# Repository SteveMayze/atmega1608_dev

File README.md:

# ATMega1608 Dev KiCad Automation

This project includes release automation for fabrication deliverables.

The automation entrypoints are intentionally stored at repository root so GitHub Actions can discover workflows correctly.

## Current automation goal

When a Git tag matching `r#.#.#` is pushed (example: `r0.1.0`), GitHub Actions will:

1. Set the KiCad text variable `RELEASE` in the project file.
2. Generate Gerber and drill files using `kicad-cli`.
3. Write deliverables to `gerber/`.
4. Upload artifacts and attach a ZIP to the GitHub release.

## Files added for automation

- `.github/workflows/release-gerbers.yml`: Release workflow triggered by version tags.
- `scripts/generate_release_artifacts.py`: Single entrypoint script for local and CI generation.
- `release-artifacts.json`: User-editable release configuration, including Gerber include layers.
- `PROJECT_TRACKING.md`: Task and roadmap tracking.

## Local usage

### Prerequisites

- KiCad installed with `kicad-cli` available on PATH.
- Python 3.9+.

If `kicad-cli` is not on PATH, set:

- macOS/Linux: `export KICAD_CLI=/full/path/to/kicad-cli`
- Windows (PowerShell): `$env:KICAD_CLI="C:\\Path\\To\\kicad-cli.exe"`

### Configure Gerber include layers

Edit `release-artifacts.json` and set:

- `project.path`: Relative path to your KiCad `.kicad_pro` file.
- `gerber.include_layers`: Layers to include in Gerber export.

Example:

```json
{
	"project": {
		"path": "kicad/ATMega1608_Dev/ATMega1608_Dev.kicad_pro"
	},
	"gerber": {
		"include_layers": [
			"F.Cu",
			"B.Cu",
			"F.Mask",
			"B.Mask",
			"F.SilkS",
			"B.SilkS",
			"Edge.Cuts"
		]
	}
}
```

This list is passed to `kicad-cli` as the `--layers` argument.
The script validates configured layer names against the board's `(layers ...)` list in the PCB file and fails early if any configured layer is invalid.

### Generate Gerbers for a release tag

```bash
python3 scripts/generate_release_artifacts.py --tag r0.1.0
```

This will update `RELEASE` to `0.1.0` and generate output in `gerber/`.

If needed, `--project` can still be passed to override `project.path` from config.

### Generate without updating `RELEASE`

```bash
python3 scripts/generate_release_artifacts.py --tag r0.1.0 --no-update-release-variable
```

### Dry run (no generation, just prints commands)

```bash
python3 scripts/generate_release_artifacts.py --tag r0.1.0 --dry-run
```

## Release trigger

Push a release tag:

```bash
git tag r0.1.0
git push origin r0.1.0
```

The workflow runs automatically for tags matching `r*.*.*`.

## CI KiCad version

This project currently targets a KiCad 10 board file format, so CI installs KiCad nightly in
GitHub Actions before generating artifacts.

The workflow uses `release-artifacts.json` for project discovery and does not hardcode the
`.kicad_pro` location.

## Future extension

The script already includes optional flags for future needs:

- `--schematic-pdf` to export schematic PDF.
- `--board-pdf` to export PCB layout PDF.

These are optional now and can be enabled later in the workflow.

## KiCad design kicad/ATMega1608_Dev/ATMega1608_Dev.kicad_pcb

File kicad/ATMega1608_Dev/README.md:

# ATMega1608 Dev KiCad Automation

This project includes release automation for fabrication deliverables.

## Current automation goal

When a Git tag matching `r#.#.#` is pushed (example: `r0.1.0`), GitHub Actions will:

1. Set the KiCad text variable `RELEASE` in the project file.
2. Generate Gerber and drill files using `kicad-cli`.
3. Write deliverables to `gerber/`.
4. Upload artifacts and attach a ZIP to the GitHub release.

## Files added for automation

- `.github/workflows/release-gerbers.yml`: Release workflow triggered by version tags.
- `scripts/generate_release_artifacts.py`: Single entrypoint script for local and CI generation.
- `release-artifacts.json`: User-editable release configuration, including Gerber include layers.
- `PROJECT_TRACKING.md`: Task and roadmap tracking.

## Local usage

### Prerequisites

- KiCad installed with `kicad-cli` available on PATH.
- Python 3.9+.

If `kicad-cli` is not on PATH, set:

- macOS/Linux: `export KICAD_CLI=/full/path/to/kicad-cli`
- Windows (PowerShell): `$env:KICAD_CLI="C:\\Path\\To\\kicad-cli.exe"`

### Configure Gerber include layers

Edit `release-artifacts.json` and set `gerber.include_layers` to match your manufacturing output needs.

Example:

```json
{
	"gerber": {
		"include_layers": [
			"F.Cu",
			"B.Cu",
			"F.Mask",
			"B.Mask",
			"F.SilkS",
			"B.SilkS",
			"Edge.Cuts"
		]
	}
}
```

This list is passed to `kicad-cli` as the `--layers` argument.
The script validates configured layer names against the board's `(layers ...)` list in the PCB file and fails early if any configured layer is invalid.

### Generate Gerbers for a release tag

```bash
python3 scripts/generate_release_artifacts.py --tag r0.1.0
```

This will update `RELEASE` to `0.1.0` and generate output in `gerber/`.

### Generate without updating `RELEASE`

```bash
python3 scripts/generate_release_artifacts.py --tag r0.1.0 --no-update-release-variable
```

### Dry run (no generation, just prints commands)

```bash
python3 scripts/generate_release_artifacts.py --tag r0.1.0 --dry-run
```

## Release trigger

Push a release tag:

```bash
git tag r0.1.0
git push origin r0.1.0
```

The workflow runs automatically for tags matching `r*.*.*`.

## Future extension

The script already includes optional flags for future needs:

- `--schematic-pdf` to export schematic PDF.
- `--board-pdf` to export PCB layout PDF.

These are optional now and can be enabled later in the workflow.

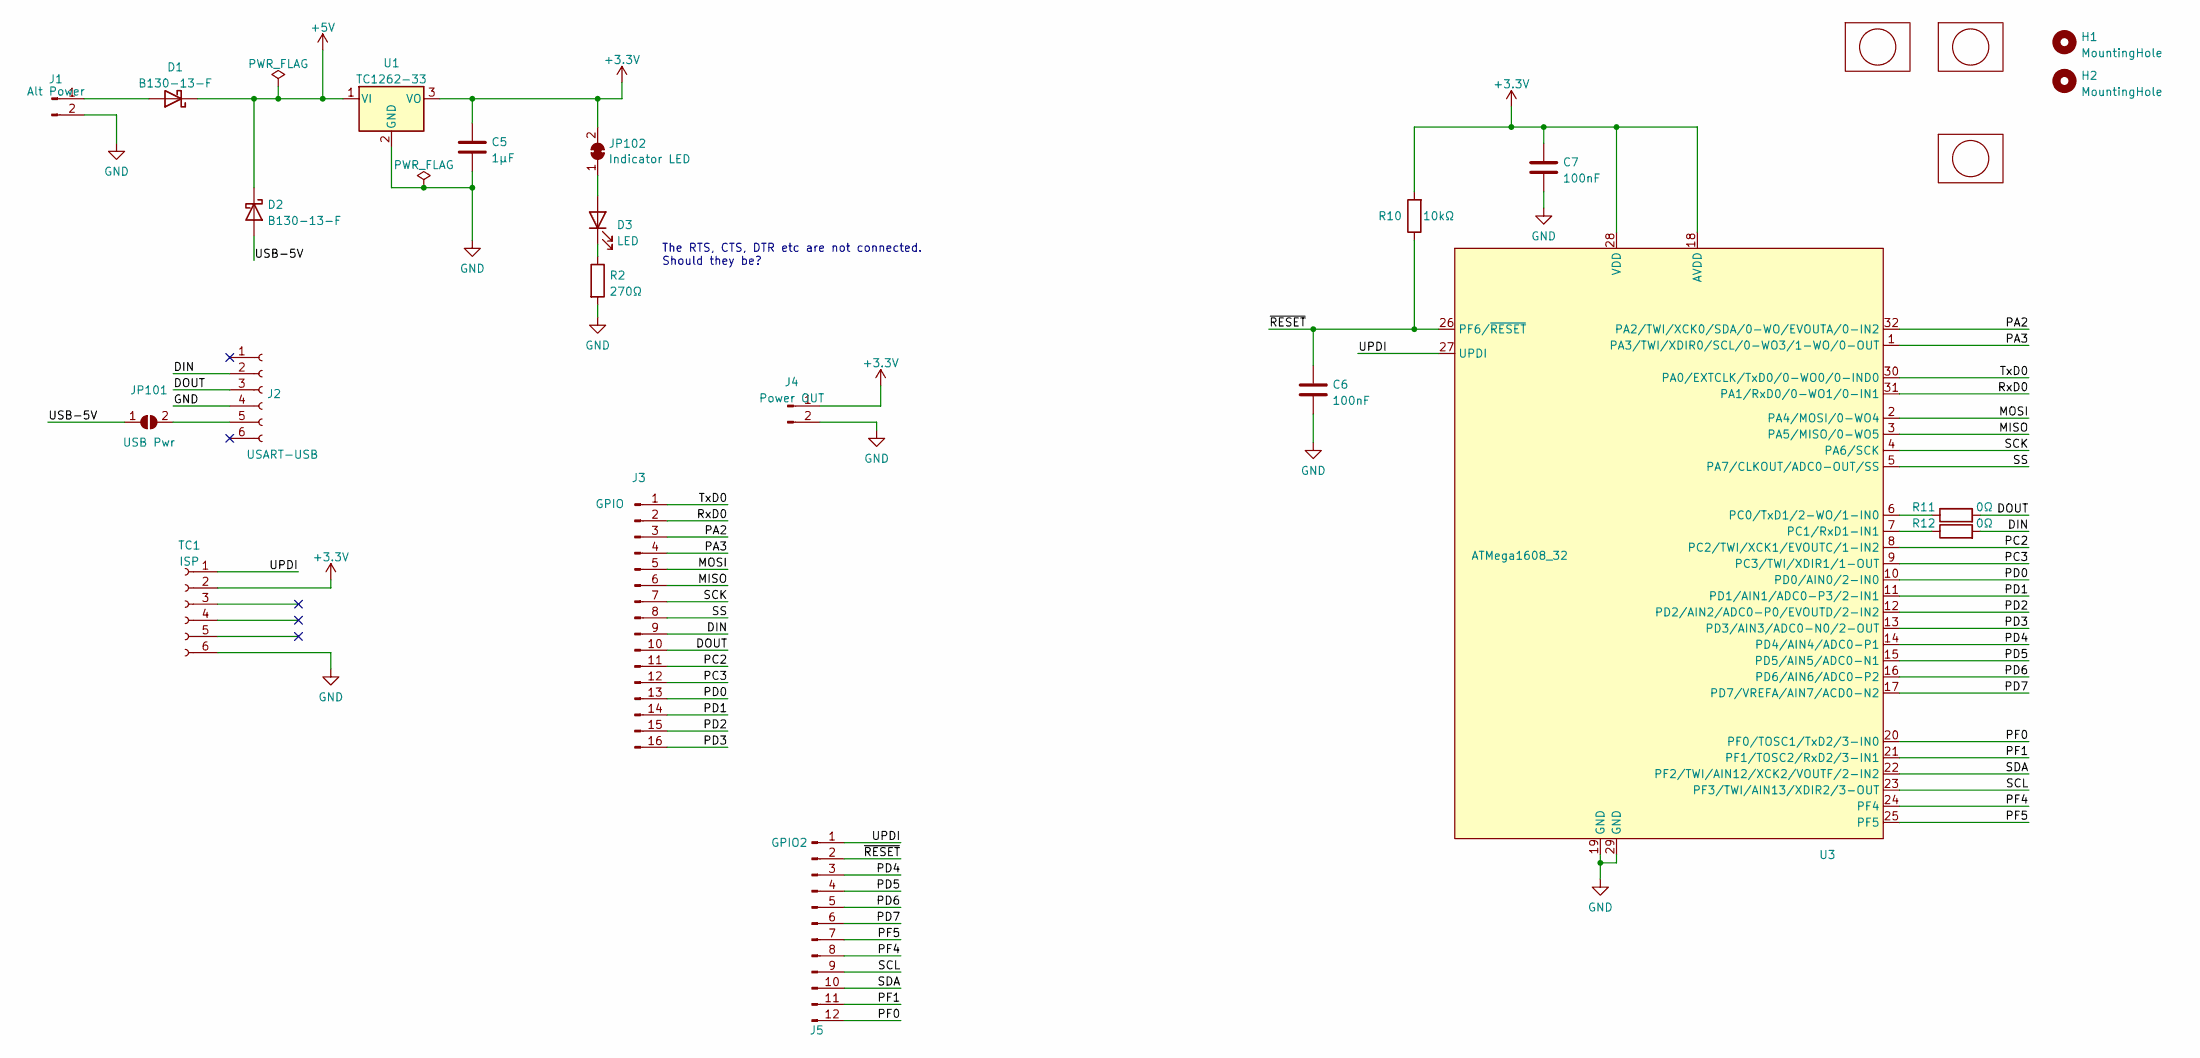
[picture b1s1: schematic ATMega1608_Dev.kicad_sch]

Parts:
C5: 1μF; C_0805_2012Metric_Pad1.18x1.45mm_HandSolder
C6, C7: 100nF; C_0805_2012Metric
D1, D2: B130-13-F; D_SMA; MPN B130-13-F
D3: LED; LED_0805_2012Metric
H1, H2: MountingHole; MountingHole_2.7mm_M2.5
J1: Alt Power; PinHeader_1x02_P2.54mm_Vertical
J2: USART-USB; PinSocket_1x06_P2.54mm_Vertical
J3: GPIO; PinHeader_1x16_P2.54mm_Vertical
J4: Power OUT; PinHeader_1x02_P2.54mm_Vertical
J5: GPIO2; PinHeader_1x12_P2.54mm_Vertical
JP101: USB Pwr; PinHeader_1x02_P2.54mm_Vertical
JP102: Indicator LED; SolderJumper-2_P1.3mm_Bridged_RoundedPad1.0x1.5mm
LG1, LG3: logo; MyBasic_rounded_50_1
LG2: logo; KiCad-Logo_5mm_SilkScreen
R2: 270Ω; R_0805_2012Metric
R10: 10kΩ; R_0805_2012Metric
R11, R12: 0Ω; R_0805_2012Metric
TC1: ISP; Tag-Connect EC06
U1: TC1262-33; SOT-223-3_TabPin2
U3: ATMega1608_32; TQFP-32_7x7mm_P0.8mm

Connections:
+3.3V: C5.1, C7.1, J4.1, JP102.2 (B), R10.2, TC1.2, U1.3 (VO), U3.18 (AVDD), U3.28 (VDD)
+5V: D1.1 (K), D2.1 (K), U1.1 (VI)
/DIN: J2.2, J3.9, R12.2
/DOUT: J2.3, J3.10, R11.2
/MISO: J3.6, U3.3 (PA5/MISO/0-WO5)
/MOSI: J3.5, U3.2 (PA4/MOSI/0-WO4)
/PA2: J3.3, U3.32 (PA2/TWI/XCK0/SDA/0-WO/EVOUTA/0-IN2)
/PA3: J3.4, U3.1 (PA3/TWI/XDIR0/SCL/0-WO3/1-WO/0-OUT)
/PC2: J3.11, U3.8 (PC2/TWI/XCK1/EVOUTC/1-IN2)
/PC3: J3.12, U3.9 (PC3/TWI/XDIR1/1-OUT)
/PD0: J3.13, U3.10 (PD0/AIN0/2-IN0)
/PD1: J3.14, U3.11 (PD1/AIN1/ADC0-P3/2-IN1)
/PD2: J3.15, U3.12 (PD2/AIN2/ADC0-P0/EVOUTD/2-IN2)
/PD3: J3.16, U3.13 (PD3/AIN3/ADC0-N0/2-OUT)
/PD4: J5.3, U3.14 (PD4/AIN4/ADC0-P1)
/PD5: J5.4, U3.15 (PD5/AIN5/ADC0-N1)
/PD6: J5.5, U3.16 (PD6/AIN6/ADC0-P2)
/PD7: J5.6, U3.17 (PD7/VREFA/AIN7/ACD0-N2)
/PF0: J5.12, U3.20 (PF0/TOSC1/TxD2/3-IN0)
/PF1: J5.11, U3.21 (PF1/TOSC2/RxD2/3-IN1)
/PF4: J5.8, U3.24 (PF4)
/PF5: J5.7, U3.25 (PF5)
/RxD0: J3.2, U3.31 (PA1/RxD0/0-WO1/0-IN1)
/SCK: J3.7, U3.4 (PA6/SCK)
/SCL: J5.9, U3.23 (PF3/TWI/AIN13/XDIR2/3-OUT)
/SDA: J5.10, U3.22 (PF2/TWI/AIN12/XCK2/VOUTF/2-IN2)
/SS: J3.8, U3.5 (PA7/CLKOUT/ADC0-OUT/SS)
/TxD0: J3.1, U3.30 (PA0/EXTCLK/TxD0/0-WO0/0-IND0)
/UPDI: J5.1, TC1.1, U3.27 (UPDI)
/USB-5V: D2.2 (A), JP101.1 (A)
/~RESET: C6.1, J5.2, R10.1, U3.26 (PF6/~RESET)
GND: C5.2, C6.2, C7.2, J1.2, J2.4, J4.2, R2.2, TC1.6, U1.2 (GND), U3.19 (GND), U3.29 (GND)
unnamed: D1.2 (A), J1.1
unnamed: D3.2 (A), JP102.1 (A)
unnamed: D3.1 (K), R2.1
unnamed: J2.5, JP101.2 (B)
unnamed: R11.1, U3.6 (PC0/TxD1/2-WO/1-IN0)
unnamed: R12.1, U3.7 (PC1/RxD1-IN1)

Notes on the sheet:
The RTS, CTS, DTR etc are not connected. Should they be?

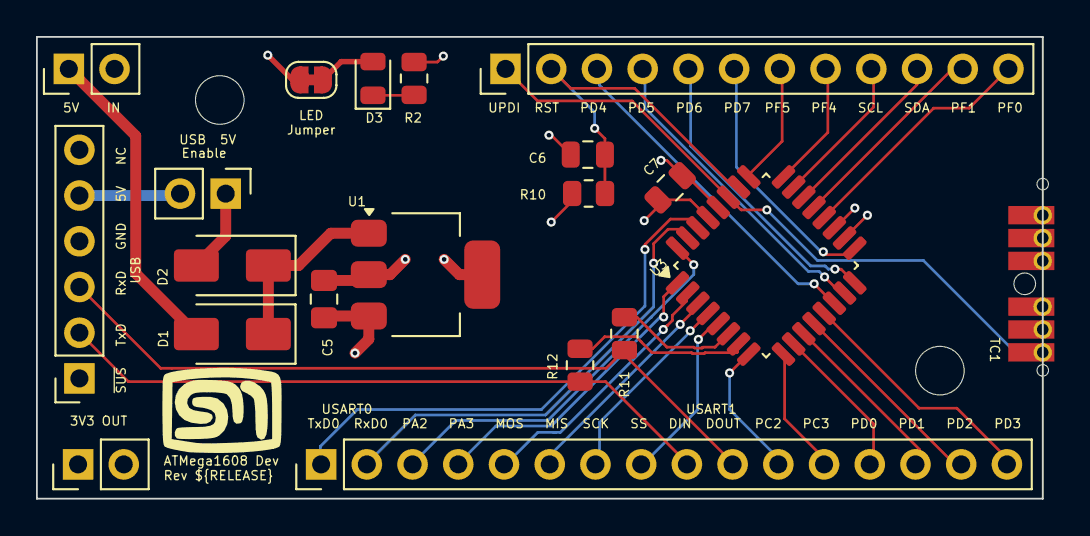
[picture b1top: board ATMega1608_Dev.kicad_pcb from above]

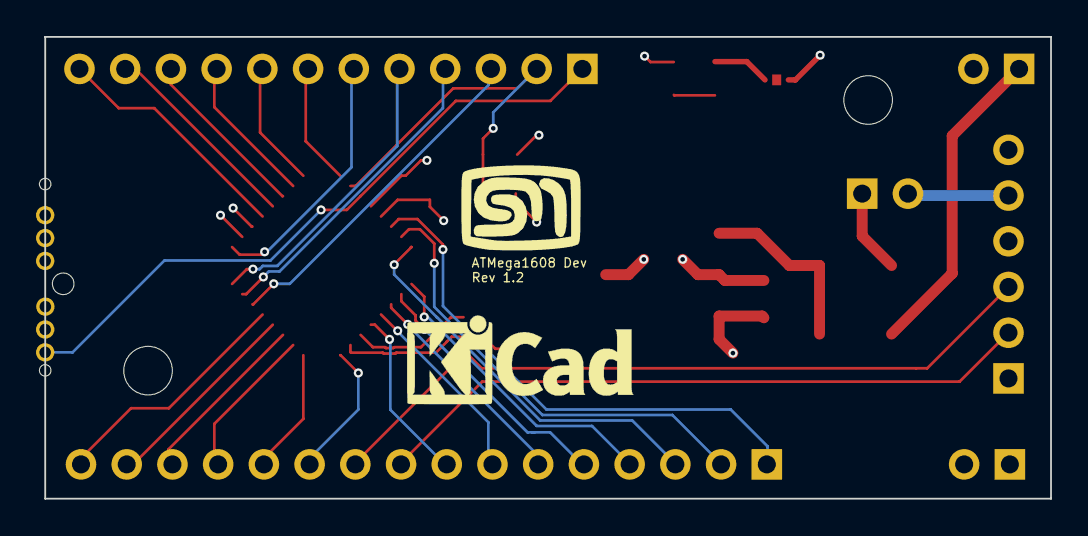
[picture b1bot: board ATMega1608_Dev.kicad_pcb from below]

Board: 4 copper layers, 55.9 x 25.7 mm, 25 parts (2 on the bottom side), 38 nets.

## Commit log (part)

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2023-01-21 Initial checkin
2023-01-21 Schematic complete
2023-01-21 Started on the layout
2023-01-22 The layout is complete - pending verification of USB interface
2023-03-05 Fixes some labeling issues
2023-03-20 Troubleshooting and diagnostic updates
2023-03-21 Move DIN R3 to top
2023-04-08 Updates to the design
2023-04-08 Refresh
2023-04-08 Removing backup zips from the repo
2023-04-08 Now ignores the backup zip files
2023-04-08 Updated gitignore for mac
2023-05-08 Removes the FT232 and replaces with a UM2102N port
2023-10-18 Adds pin allocation images
2023-11-05 Fixes label overflow
2023-11-07 Ads an SVG for further documentation
2023-12-09 Revert "Fixes label overflow"
    This reverts commit 462388ed25e35246e7662647474ba0507c06f5b0.
2023-12-09 Moved the USART_Troubleshooting changes to main
2024-01-14 Revision 1.2 - Update to connectors, jumpers and labels
2024-04-21 Revision 1.2
2026-06-03 Adding a PCB release workflow
2026-06-03 Updates to the action script
2026-06-03 Update gerber release to use nightly
2026-06-03 Prefix the project name to the gerber zip file for the release
2026-06-03 Removed the obolete gerber directory
